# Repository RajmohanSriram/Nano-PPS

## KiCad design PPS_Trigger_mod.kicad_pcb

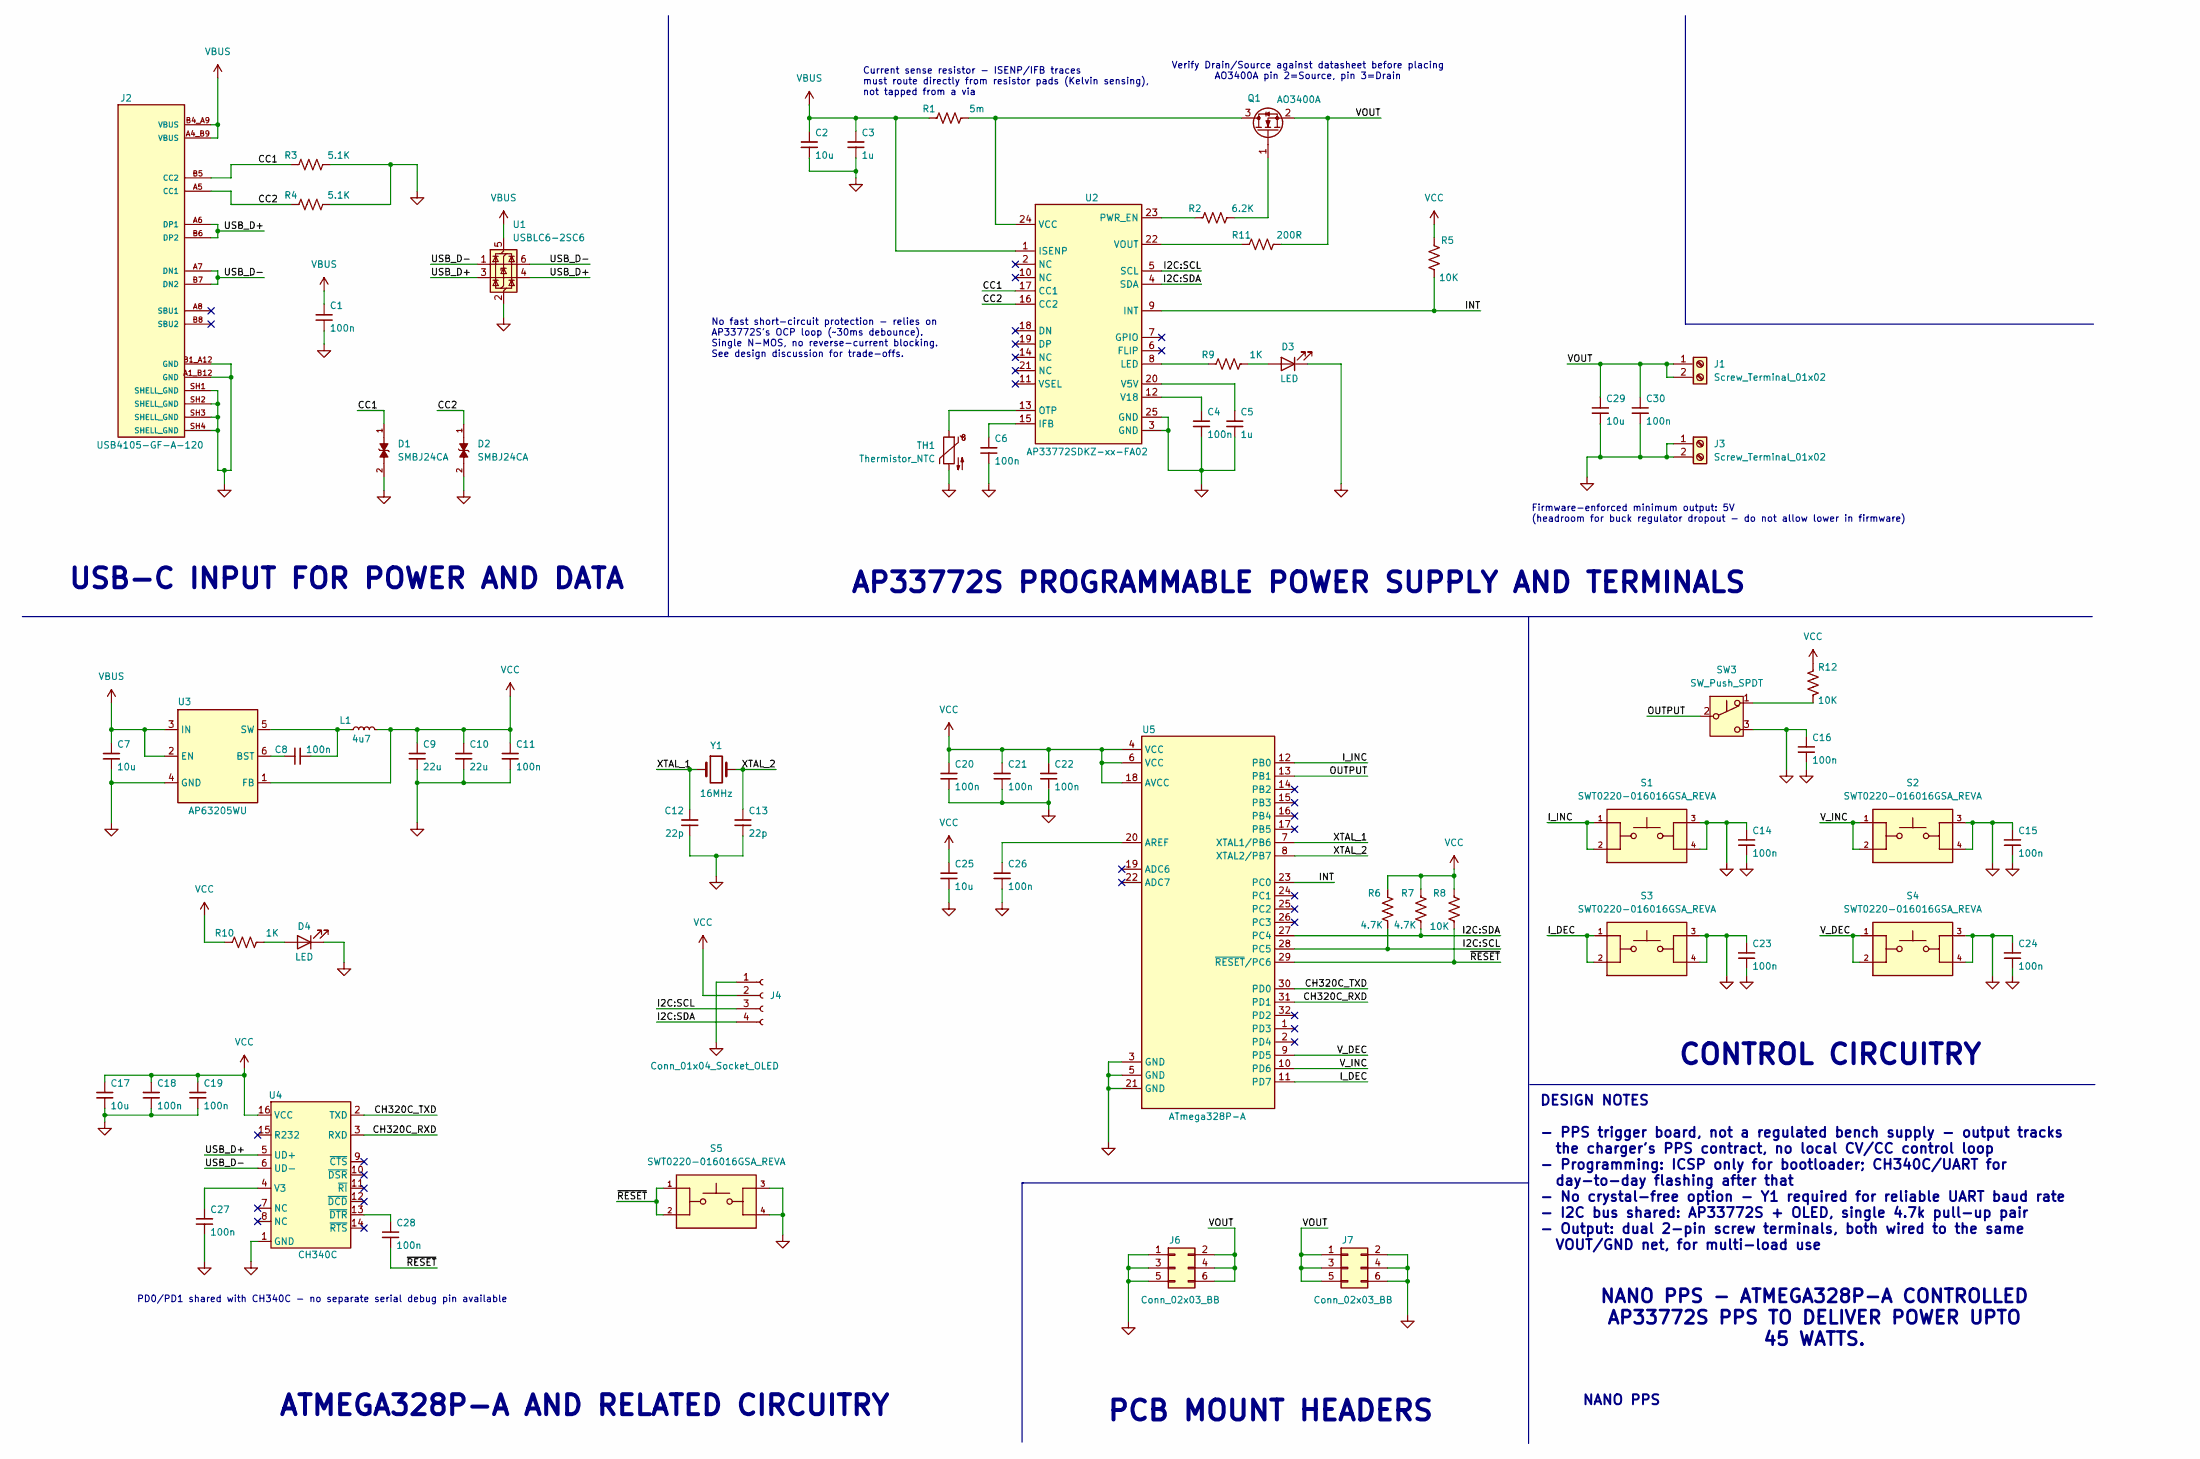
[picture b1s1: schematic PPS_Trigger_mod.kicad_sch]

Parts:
C1, C30: 100n; C_0805_2012Metric_Pad1.18x1.45mm_HandSolder
C2, C7, C17, C25, C29: 10u; C_0805_2012Metric_Pad1.18x1.45mm_HandSolder
C3: 1u; C_0805_2012Metric_Pad1.18x1.45mm_HandSolder
C4, C6, C8, C11, C14, C15, C16, C18, C19, C20, C21, C22, C23, C24, C26, C27, C28: 100n; C_0603_1608Metric_Pad1.08x0.95mm_HandSolder
C5: 1u; C_0603_1608Metric_Pad1.08x0.95mm_HandSolder
C9, C10: 22u; C_1210_3225Metric_Pad1.33x2.70mm_HandSolder
C12, C13: 22p; C_0603_1608Metric_Pad1.08x0.95mm_HandSolder
D1, D2: SMBJ24CA; DIOM4336X265N; PARTREV I2102
D3, D4: LED; LED_0603_1608Metric_Pad1.05x0.95mm_HandSolder
J1, J3: Screw_Terminal_01x02; TerminalBlock_MaiXu_MX126-5.0-02P_1x02_P5.00mm
J2: USB4105-GF-A-120; GCT_USB4105-GF-A-120; PARTREV B3
J4: Conn_01x04_Socket_OLED; PinSocket_1x04_P2.54mm_Vertical
J6, J7: Conn_02x03_BB; PinHeader_2x03_P2.54mm_Vertical
L1: 4u7; L_APV_ANR6045
Q1: AO3400A; SOT-23
R1: 5m; R_1206_3216Metric_Pad1.30x1.75mm_HandSolder
R2: 6.2K; R_0603_1608Metric_Pad0.98x0.95mm_HandSolder
R3, R4: 5.1K; R_0603_1608Metric_Pad0.98x0.95mm_HandSolder
R5, R8, R12: 10K; R_0603_1608Metric_Pad0.98x0.95mm_HandSolder
R6, R7: 4.7K; R_0603_1608Metric_Pad0.98x0.95mm_HandSolder
R9, R10: 1K; R_0603_1608Metric_Pad0.98x0.95mm_HandSolder
R11: 200R; R_0603_1608Metric_Pad0.98x0.95mm_HandSolder
S1, S2, S3, S4, S5: SWT0220-016016GSA_REVA; SW_SWT0220-016016GSA_REVA; PARTREV A
SW3: SW_Push_SPDT; SW_Slide_SPDT_Straight_CK_OS102011MS2Q
TH1: Thermistor_NTC; R_Axial_DIN0204_L3.6mm_D1.6mm_P7.62mm_Horizontal
U1: USBLC6-2SC6; SOT-23-6
U2: AP33772SDKZ-xx-FA02; Texas_RTW_WQFN-24-1EP_4x4mm_P0.5mm_EP2.7x2.7mm
U3: AP63205WU; TSOT-23-6
U4: CH340C; SOIC-16_3.9x9.9mm_P1.27mm
U5: ATmega328P-A; TQFP-32_7x7mm_P0.8mm
Y1: 16MHz; Crystal_SMD_HC49-SD

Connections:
/CC1: D1.1, J2.B5 (CC2), R3.1, U2.17 (CC1)
/CC2: D2.1, J2.A5 (CC1), R4.1, U2.16 (CC2)
/CH320C_RXD: U4.3 (RXD), U5.31 (PD1)
/CH320C_TXD: U4.2 (TXD), U5.30 (PD0)
/I2C:SCL: J4.3, R6.1, U2.5 (SCL), U5.28 (PC5)
/I2C:SDA: J4.4, R7.1, U2.4 (SDA), U5.27 (PC4)
/INT: R5.1, U2.9 (INT), U5.23 (PC0)
/I_DEC: S3.1, S3.2, U5.11 (PD7)
/I_INC: S1.1, S1.2, U5.12 (PB0)
/OUTPUT: SW3.2 (B), U5.13 (PB1)
/USB_D+: J2.A6 (DP1), J2.B6 (DP2), U1.3 (I/O2), U1.4 (I/O2), U4.5 (UD+)
/USB_D-: J2.A7 (DN1), J2.B7 (DN2), U1.1 (I/O1), U1.6 (I/O1), U4.6 (UD-)
/VOUT: C29.1, C30.1, J1.1, J1.2, J6.2, J6.4, J6.6, J7.1, J7.3, J7.5, Q1.2 (S), R11.2
/V_DEC: S4.1, S4.2, U5.9 (PD5)
/V_INC: S2.1, S2.2, U5.10 (PD6)
/XTAL_1: C12.1, U5.7 (XTAL1/PB6), Y1.1
/XTAL_2: C13.1, U5.8 (XTAL2/PB7), Y1.2
/~RESET: C28.2, R8.1, S5.1, S5.2, U5.29 (~RESET/PC6)
GND: C1.2, C2.2, C3.2, C4.2, C5.2, C6.2, C7.2, C9.2, C10.2, C11.2, C12.2, C13.2, C14.1, C14.2, C15.1, C15.2, C16.1, C16.2, C17.2, C18.2, C19.2, C20.2, C21.2, C22.2, C23.1, C23.2, C24.1, C24.2, C25.2, C26.2, C27.2, C29.2, C30.2, D1.2, D2.2, D3.1 (K), D4.1 (K), J2.A1_B12 (GND), J2.B1_A12 (GND), J2.SH1 (SHELL_GND), J2.SH2 (SHELL_GND), J2.SH3 (SHELL_GND), J2.SH4 (SHELL_GND), J3.1, J3.2, J4.1, J6.1, J6.3, J6.5, J7.2, J7.4, J7.6, R3.2, R4.2, S1.3, S1.4, S2.3, S2.4, S3.3, S3.4, S4.3, S4.4, S5.3, S5.4, SW3.3 (C), TH1.2, U1.2 (GND), U2.3 (GND), U2.25 (GND), U3.4 (GND), U4.1 (GND), U5.3 (GND), U5.5 (GND), U5.21 (GND)
unnamed: D3.2 (A), R9.2
unnamed: D4.2 (A), R10.2
unnamed: Q1.3 (D), R1.2, U2.24 (VCC)
unnamed: Q1.1 (G), R2.2
unnamed: R12.1, SW3.1 (A)
unnamed: C6.1, U2.15 (IFB)
unnamed: R9.1, U2.8 (LED)
unnamed: TH1.1, U2.13 (OTP)
unnamed: R2.1, U2.23 (PWR_EN)
unnamed: C5.1, U2.20 (V5V)
unnamed: C4.1, U2.12 (V18)
unnamed: R11.1, U2.22 (VOUT)
unnamed: C8.1, U3.6 (BST)
unnamed: C8.2, L1.1, U3.5 (SW)
unnamed: C27.1, U4.4 (V3)
unnamed: C28.1, U4.13 (~DTR)
unnamed: C26.1, U5.20 (AREF)
VBUS: C1.1, C2.1, C3.1, C7.1, J2.A4_B9 (VBUS), J2.B4_A9 (VBUS), R1.1, U1.5 (VBUS), U2.1 (ISENP), U3.2 (EN), U3.3 (IN)
VCC: C9.1, C10.1, C11.1, C17.1, C18.1, C19.1, C20.1, C21.1, C22.1, C25.1, J4.2, L1.2, R5.2, R6.2, R7.2, R8.2, R10.1, R12.2, U3.1 (FB), U4.16 (VCC), U5.4 (VCC), U5.6 (VCC), U5.18 (AVCC)

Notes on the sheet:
CONTROL CIRCUITRY
Verify Drain/Source against datasheet before placing AO3400A pin 2=Source, pin 3=Drain
PCB MOUNT HEADERS
PD0/PD1 shared with CH340C - no separate serial debug pin available
NANO PPS
AP33772S PROGRAMMABLE POWER SUPPLY AND TERMINALS
USB-C INPUT FOR POWER AND DATA
DESIGN NOTES - PPS trigger board, not a regulated bench supply - output tracks the charger's PPS contract, no local CV/CC control loop - Programming: ICSP only for bootloader; CH340C/UART for day-to-day flashing after that - No crystal-free option - Y1 required for reliable UART baud rate - I2C bus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
ATMEGA328P-A AND RELATED CIRCUITRY
NANO PPS - ATMEGA328P-A CONTROLLED AP33772S PPS TO DELIVER POWER UPTO 45 WATTS.
No fast short-circuit protection - relies on AP33772S's OCP loop (~30ms debounce). Single N-MOS, no reverse-current blocking. See design discussion for trade-offs.
Firmware-enforced minimum output: 5V (headroom for buck regulator dropout - do not allow lower in firmware)
Current sense resistor - ISENP/IFB traces must route directly from resistor pads (Kelvin sensing), not tapped from a via

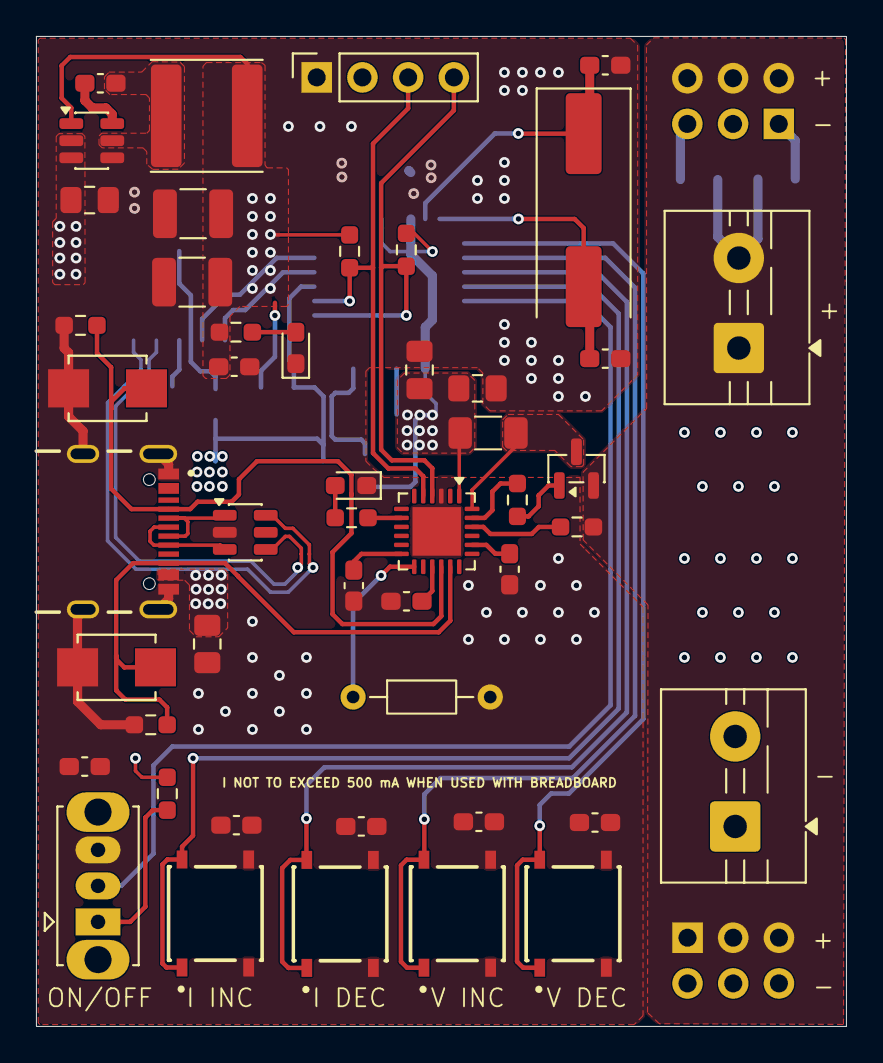
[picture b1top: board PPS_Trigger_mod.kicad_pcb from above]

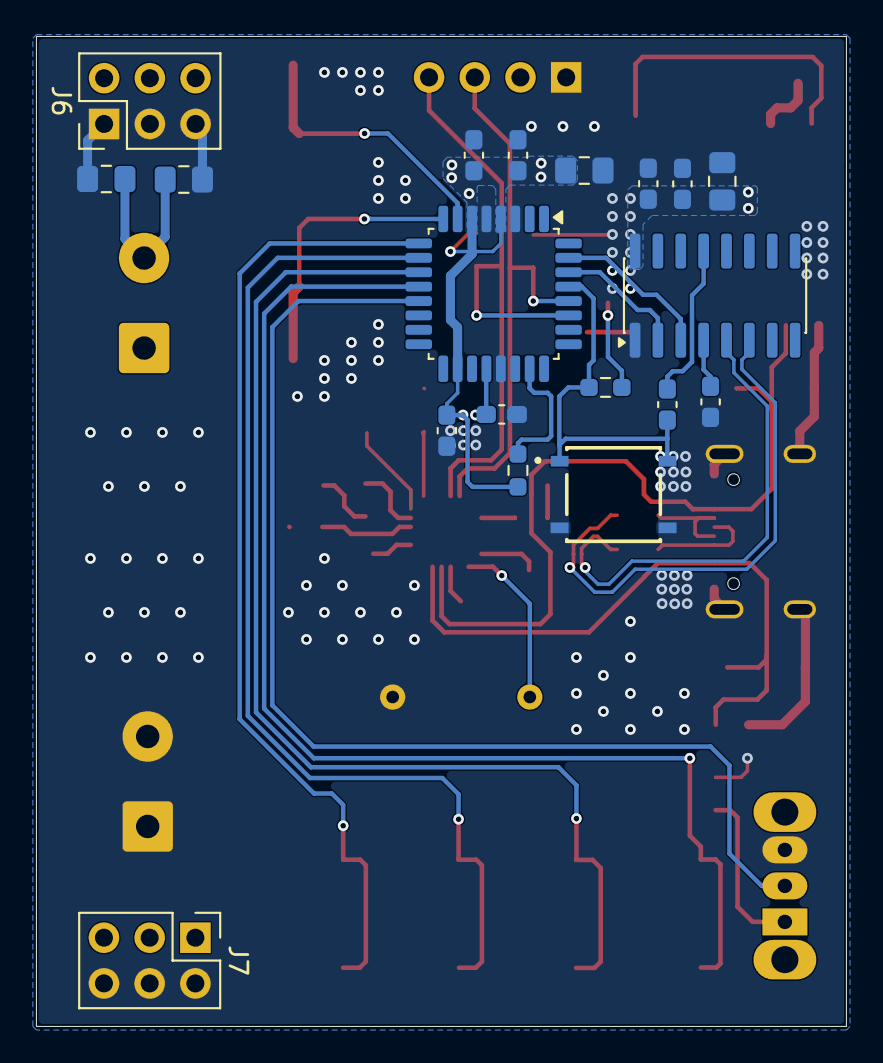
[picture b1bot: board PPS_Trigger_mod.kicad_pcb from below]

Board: 4 copper layers, 45.0 x 55.0 mm, 67 parts (19 on the bottom side), 38 nets.
